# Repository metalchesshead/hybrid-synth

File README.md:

Analog/Digital Hybrid Synthesizer

How to use:
1. Draw wave envelope
2. Upload to board

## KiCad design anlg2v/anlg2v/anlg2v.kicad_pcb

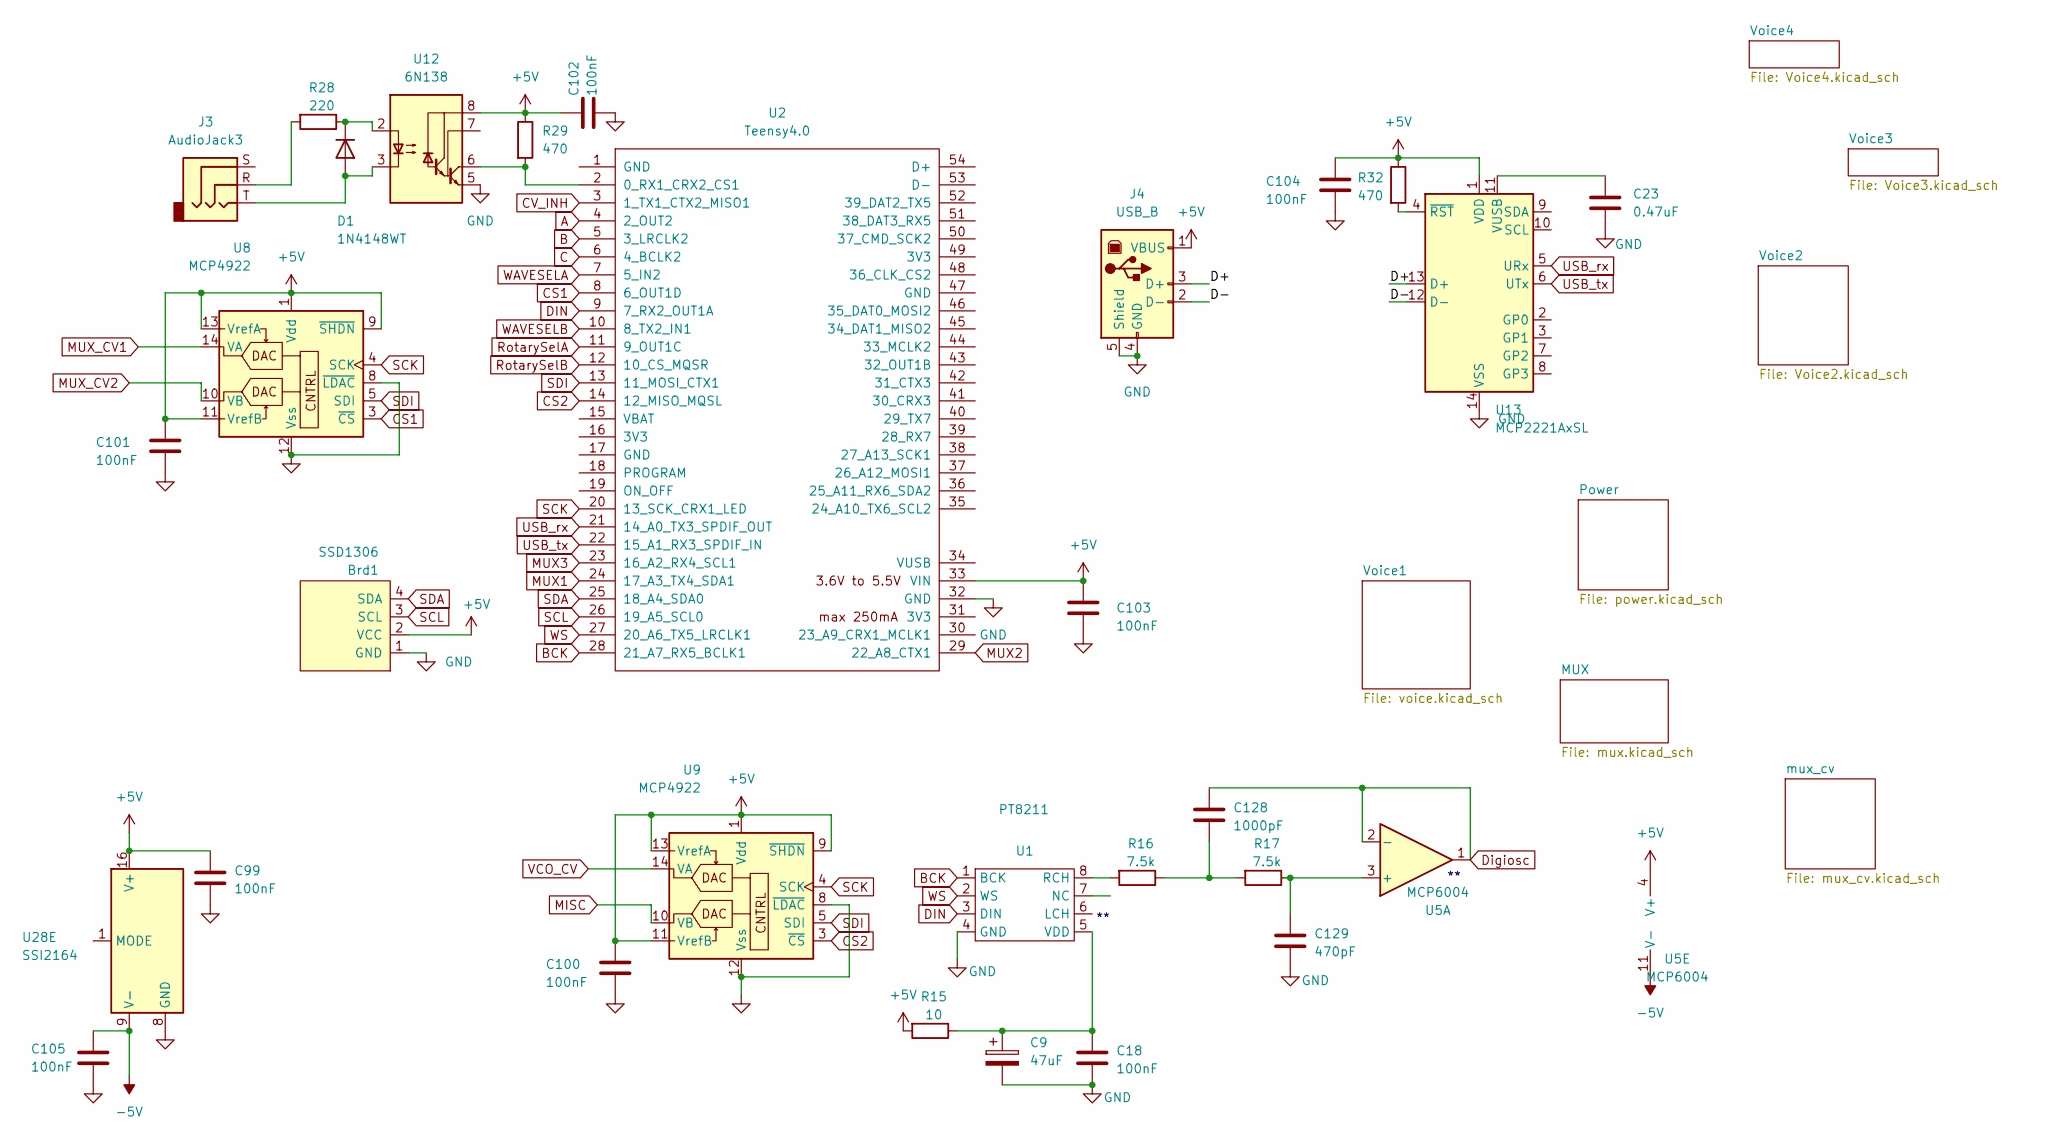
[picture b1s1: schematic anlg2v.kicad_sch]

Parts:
Brd1: SSD1306; 128x64OLED
C9: 47uF; CP_Radial_D10.0mm_P5.00mm
C18, C99, C100, C101, C102, C103, C104, C105: 100nF; C_0402_1005Metric_Pad0.74x0.62mm_HandSolder
C23: 0.47uF; C_0402_1005Metric_Pad0.74x0.62mm_HandSolder
C128: 1000pF; C_0402_1005Metric_Pad0.74x0.62mm_HandSolder
C129: 470pF; C_0402_1005Metric_Pad0.74x0.62mm_HandSolder
D1: 1N4148WT; D_SOD-523
J3: AudioJack3; PJ-307
J4: USB_B; USB_B_Lumberg_2411_02_Horizontal
R15: 10; R_0402_1005Metric
R16, R17: 7.5k; R_0402_1005Metric
R28: 220; R_0402_1005Metric
R29, R32: 470; R_0402_1005Metric
U1: PT8211; SOP-8_3.76x4.96mm_P1.27mm
U2: Teensy4.0; Teensy40
U5: MCP6004; SOIC-14_3.9x8.7mm_P1.27mm
U8, U9: MCP4922; SOIC-14_3.9x8.7mm_P1.27mm
U12: 6N138; DIP-8_W7.62mm_Socket
U13: MCP2221AxSL; SOIC-14_3.9x8.7mm_P1.27mm
U28: SSI2164; SOP-16_3.9x9.9mm_P1.27mm

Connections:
+5V: Brd1.2 (VCC), C99.1, C100.1, C101.1, C102.1, C103.1, C104.1, J4.1 (VBUS), R15.2, R29.1, R32.1, U2.33 (VIN), U5.4 (V+), U8.1 (Vdd), U8.9 (~SHDN), U8.11 (VrefB), U8.13 (VrefA), U9.1 (Vdd), U9.9 (~SHDN), U9.11 (VrefB), U9.13 (VrefA), U12.8 (VCC), U13.1 (VDD), U28.16 (V+); also elsewhere on the board
-5V: C105.1, U5.11 (V-), U28.9 (V-); also elsewhere on the board
/D+: J4.3 (D+), U13.13 (D+)
/D-: J4.2 (D-), U13.12 (D-)
A: U2.4 (2_OUT2); also elsewhere on the board
B: U2.5 (3_LRCLK2); also elsewhere on the board
BCK: U1.1 (BCK), U2.28 (21_A7_RX5_BCLK1)
C: U2.6 (4_BCLK2); also elsewhere on the board
CS1: U2.8 (6_OUT1D), U8.3 (~CS)
CS2: U2.14 (12_MISO_MQSL), U9.3 (~CS)
CV_INH: U2.3 (1_TX1_CTX2_MISO1); also elsewhere on the board
DIN: U1.3 (DIN), U2.9 (7_RX2_OUT1A)
GND: Brd1.1 (GND), C9.2, C18.2, C23.2, C99.2, C100.2, C101.2, C102.2, C103.2, C104.2, C105.2, C129.2, J4.4 (GND), J4.5 (Shield), U1.4 (GND), U1.6 (LCH), U2.32 (GND), U8.8 (~LDAC), U8.12 (Vss), U9.8 (~LDAC), U9.12 (Vss), U12.5 (GND), U13.14 (VSS), U28.8 (GND); also elsewhere on the board
MISC: U9.10 (VB)
MUX1: U2.24 (17_A3_TX4_SDA1); also elsewhere on the board
MUX2: U2.29 (22_A8_CTX1); also elsewhere on the board
MUX3: U2.23 (16_A2_RX4_SCL1); also elsewhere on the board
MUX_CV1: U8.14 (VA); also elsewhere on the board
MUX_CV2: U8.10 (VB); also elsewhere on the board
unnamed 22: C128.2, R16.1, R17.2; also elsewhere on the board
unnamed: D1.2 (A), J3.T, U12.3 (C2)
unnamed: D1.1 (K), R28.1, U12.2 (C1)
unnamed: J3.R, R28.2
unnamed: R16.2, U1.8 (RCH)
unnamed: C9.1, C18.1, R15.1, U1.5 (VDD)
unnamed: R29.2, U2.2 (0_RX1_CRX2_CS1), U12.6 (VO2)
unnamed: C23.1, U13.11 (VUSB)
unnamed: R32.2, U13.4 (~RST)
RotarySelA: U2.11 (9_OUT1C); also elsewhere on the board
RotarySelB: U2.12 (10_CS_MQSR); also elsewhere on the board
SCK: U2.20 (13_SCK_CRX1_LED), U8.4 (SCK), U9.4 (SCK)
SCL: Brd1.3 (SCL), U2.26 (19_A5_SCL0)
SDA: Brd1.4 (SDA), U2.25 (18_A4_SDA0)
SDI: U2.13 (11_MOSI_CTX1), U8.5 (SDI), U9.5 (SDI)
USB_rx: U2.21 (14_A0_TX3_SPDIF_OUT), U13.5 (URx)
USB_tx: U2.22 (15_A1_RX3_SPDIF_IN), U13.6 (UTx)
VCO_CV: U9.14 (VA); also elsewhere on the board
WAVESELA: U2.7 (5_IN2); also elsewhere on the board
WAVESELB: U2.10 (8_TX2_IN1); also elsewhere on the board
WS: U1.2 (WS), U2.27 (20_A6_TX5_LRCLK1)

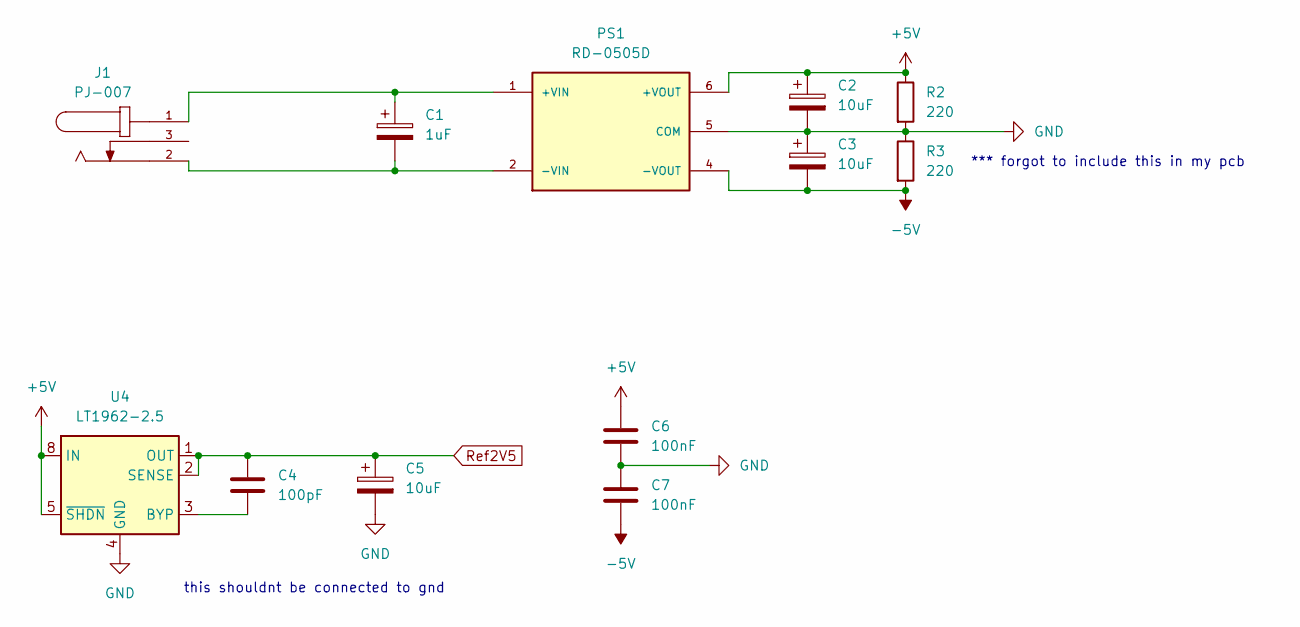
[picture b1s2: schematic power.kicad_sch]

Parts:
C1: 1uF; CP_Radial_D10.0mm_P5.00mm
C2, C3, C5: 10uF; CP_Radial_D10.0mm_P5.00mm
C4: 100pF; C_0402_1005Metric_Pad0.74x0.62mm_HandSolder
C6, C7: 100nF; C_0402_1005Metric_Pad0.74x0.62mm_HandSolder
J1: PJ-007; SAMESKY_PJ-007; PARTREV 1.07
PS1: RD-0505D; CONV_RD-0505D; PARTREV 1
R2, R3: 220; R_0402_1005Metric
U4: LT1962-2.5; MSOP-8_3x3mm_P0.65mm

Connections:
+5V: C2.1, C6.1, PS1.6 (+VOUT), R2.1, U4.5 (~SHDN), U4.8 (IN); also elsewhere on the board
-5V: C3.2, C7.2, PS1.4 (-VOUT), R3.2; also elsewhere on the board
GND: C2.2, C3.1, C5.2, C6.2, C7.1, PS1.5 (COM), R2.2, R3.1, U4.4 (GND); also elsewhere on the board
unnamed: C1.1, J1.1, PS1.1 (+VIN)
unnamed: C1.2, J1.2, PS1.2 (-VIN)
unnamed: C4.2, U4.3 (BYP)
Ref2V5: C4.1, C5.1, U4.1 (OUT), U4.2 (SENSE); also elsewhere on the board

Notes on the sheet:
this shouldnt be connected to gnd
*** forgot to include this in my pcb

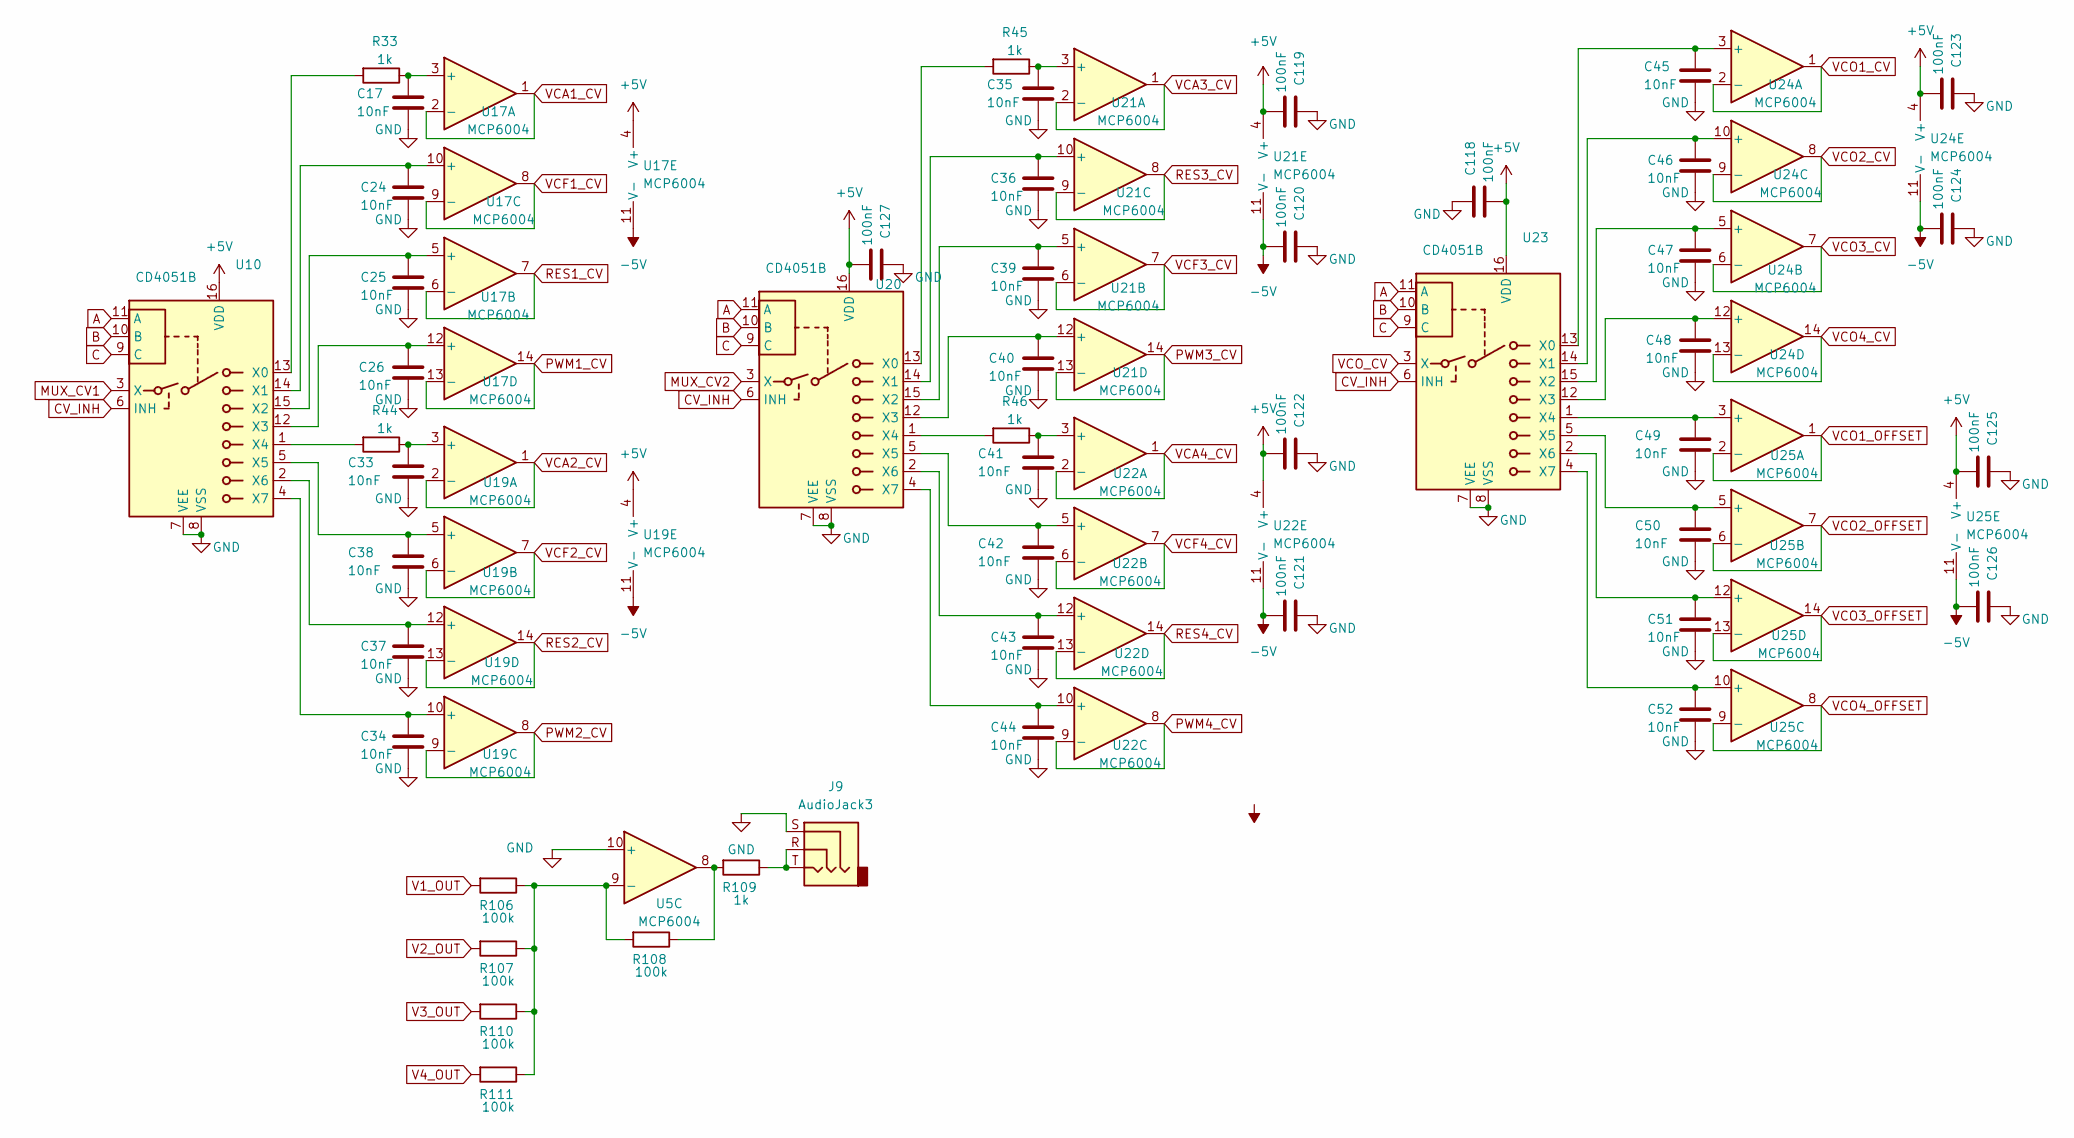
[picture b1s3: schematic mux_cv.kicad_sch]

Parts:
C17, C24, C25, C26, C33, C34, C35, C36, C37, C38, C39, C40, C41, C42, C43, C44, C45, C46, C47, C48, C49, C50, C51, C52: 10nF; C_0402_1005Metric_Pad0.74x0.62mm_HandSolder
C118, C119, C120, C121, C122, C123, C124, C125, C126, C127: 100nF; C_0402_1005Metric_Pad0.74x0.62mm_HandSolder
J9: AudioJack3; PJ-307
R33, R44, R45, R46, R109: 1k; R_0402_1005Metric
R106, R107, R108, R110, R111: 100k; R_0402_1005Metric
U5, U17, U19, U21, U22, U24, U25: MCP6004; SOIC-14_3.9x8.7mm_P1.27mm
U10, U20, U23: CD4051B; SOIC-16_3.9x9.9mm_P1.27mm

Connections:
+5V: C118.2, C119.2, C122.2, C123.2, C125.2, C127.2, U10.16 (VDD), U17.4 (V+), U19.4 (V+), U20.16 (VDD), U21.4 (V+), U22.4 (V+), U23.16 (VDD), U24.4 (V+), U25.4 (V+); also elsewhere on the board
-5V: C120.2, C121.2, C124.2, C126.2, U17.11 (V-), U19.11 (V-), U21.11 (V-), U22.11 (V-), U24.11 (V-), U25.11 (V-); also elsewhere on the board
A: U10.11 (A), U20.11 (A), U23.11 (A); also elsewhere on the board
B: U10.10 (B), U20.10 (B), U23.10 (B); also elsewhere on the board
C: U10.9 (C), U20.9 (C), U23.9 (C); also elsewhere on the board
CV_INH: U10.6 (INH), U20.6 (INH), U23.6 (INH); also elsewhere on the board
GND: C17.2, C24.2, C25.2, C26.2, C33.2, C34.2, C35.2, C36.2, C37.2, C38.2, C39.2, C40.2, C41.2, C42.2, C43.2, C44.2, C45.2, C46.2, C47.2, C48.2, C49.2, C50.2, C51.2, C52.2, C118.1, C119.1, C120.1, C121.1, C122.1, C123.1, C124.1, C125.1, C126.1, C127.1, J9.S, U5.10 (+), U10.7 (VEE), U10.8 (VSS), U20.7 (VEE), U20.8 (VSS), U23.7 (VEE), U23.8 (VSS); also elsewhere on the board
MUX_CV1: U10.3 (X); also elsewhere on the board
MUX_CV2: U20.3 (X); also elsewhere on the board
unnamed: J9.R, J9.T, R109.1
unnamed: R108.1, R109.2, U5.8
unnamed: R106.1, R107.1, R108.2, R110.1, R111.1, U5.9 (-)
unnamed: R33.2, U10.13 (X0)
unnamed: C24.1, U10.14 (X1), U17.10 (+)
unnamed: C25.1, U10.15 (X2), U17.5 (+)
unnamed: C26.1, U10.12 (X3), U17.12 (+)
unnamed: R44.2, U10.1 (X4)
unnamed: C38.1, U10.5 (X5), U19.5 (+)
unnamed: C37.1, U10.2 (X6), U19.12 (+)
unnamed: C34.1, U10.4 (X7), U19.10 (+)
unnamed: C17.1, R33.1, U17.3 (+)
unnamed: C33.1, R44.1, U19.3 (+)
unnamed: R45.2, U20.13 (X0)
unnamed: C36.1, U20.14 (X1), U21.10 (+)
unnamed: C39.1, U20.15 (X2), U21.5 (+)
unnamed: C40.1, U20.12 (X3), U21.12 (+)
unnamed: R46.2, U20.1 (X4)
unnamed: C42.1, U20.5 (X5), U22.5 (+)
unnamed: C43.1, U20.2 (X6), U22.12 (+)
unnamed: C44.1, U20.4 (X7), U22.10 (+)
unnamed: C35.1, R45.1, U21.3 (+)
unnamed: C41.1, R46.1, U22.3 (+)
unnamed: C45.1, U23.13 (X0), U24.3 (+)
unnamed: C46.1, U23.14 (X1), U24.10 (+)
unnamed: C47.1, U23.15 (X2), U24.5 (+)
unnamed: C48.1, U23.12 (X3), U24.12 (+)
unnamed: C49.1, U23.1 (X4), U25.3 (+)
unnamed: C50.1, U23.5 (X5), U25.5 (+)
unnamed: C51.1, U23.2 (X6), U25.12 (+)
unnamed: C52.1, U23.4 (X7), U25.10 (+)
PWM1_CV: U17.13 (-), U17.14; also elsewhere on the board
PWM2_CV: U19.8, U19.9 (-); also elsewhere on the board
PWM3_CV: U21.13 (-), U21.14; also elsewhere on the board
PWM4_CV: U22.8, U22.9 (-); also elsewhere on the board
RES1_CV: U17.6 (-), U17.7; also elsewhere on the board
RES2_CV: U19.13 (-), U19.14; also elsewhere on the board
RES3_CV: U21.8, U21.9 (-); also elsewhere on the board
RES4_CV: U22.13 (-), U22.14; also elsewhere on the board
V1_OUT: R106.2; also elsewhere on the board
V2_OUT: R107.2; also elsewhere on the board
V3_OUT: R110.2; also elsewhere on the board
V4_OUT: R111.2; also elsewhere on the board
VCA1_CV: U17.1, U17.2 (-); also elsewhere on the board
VCA2_CV: U19.1, U19.2 (-); also elsewhere on the board
VCA3_CV: U21.1, U21.2 (-); also elsewhere on the board
VCA4_CV: U22.1, U22.2 (-); also elsewhere on the board
VCF1_CV: U17.8, U17.9 (-); also elsewhere on the board
VCF2_CV: U19.6 (-), U19.7; also elsewhere on the board
VCF3_CV: U21.6 (-), U21.7; also elsewhere on the board
VCF4_CV: U22.6 (-), U22.7; also elsewhere on the board
VCO1_CV: U24.1, U24.2 (-); also elsewhere on the board
VCO1_OFFSET: U25.1, U25.2 (-); also elsewhere on the board
VCO2_CV: U24.8, U24.9 (-); also elsewhere on the board
VCO2_OFFSET: U25.6 (-), U25.7; also elsewhere on the board
VCO3_CV: U24.6 (-), U24.7; also elsewhere on the board
VCO3_OFFSET: U25.13 (-), U25.14; also elsewhere on the board
VCO4_CV: U24.13 (-), U24.14; also elsewhere on the board
VCO4_OFFSET: U25.8, U25.9 (-); also elsewhere on the board
VCO_CV: U23.3 (X); also elsewhere on the board

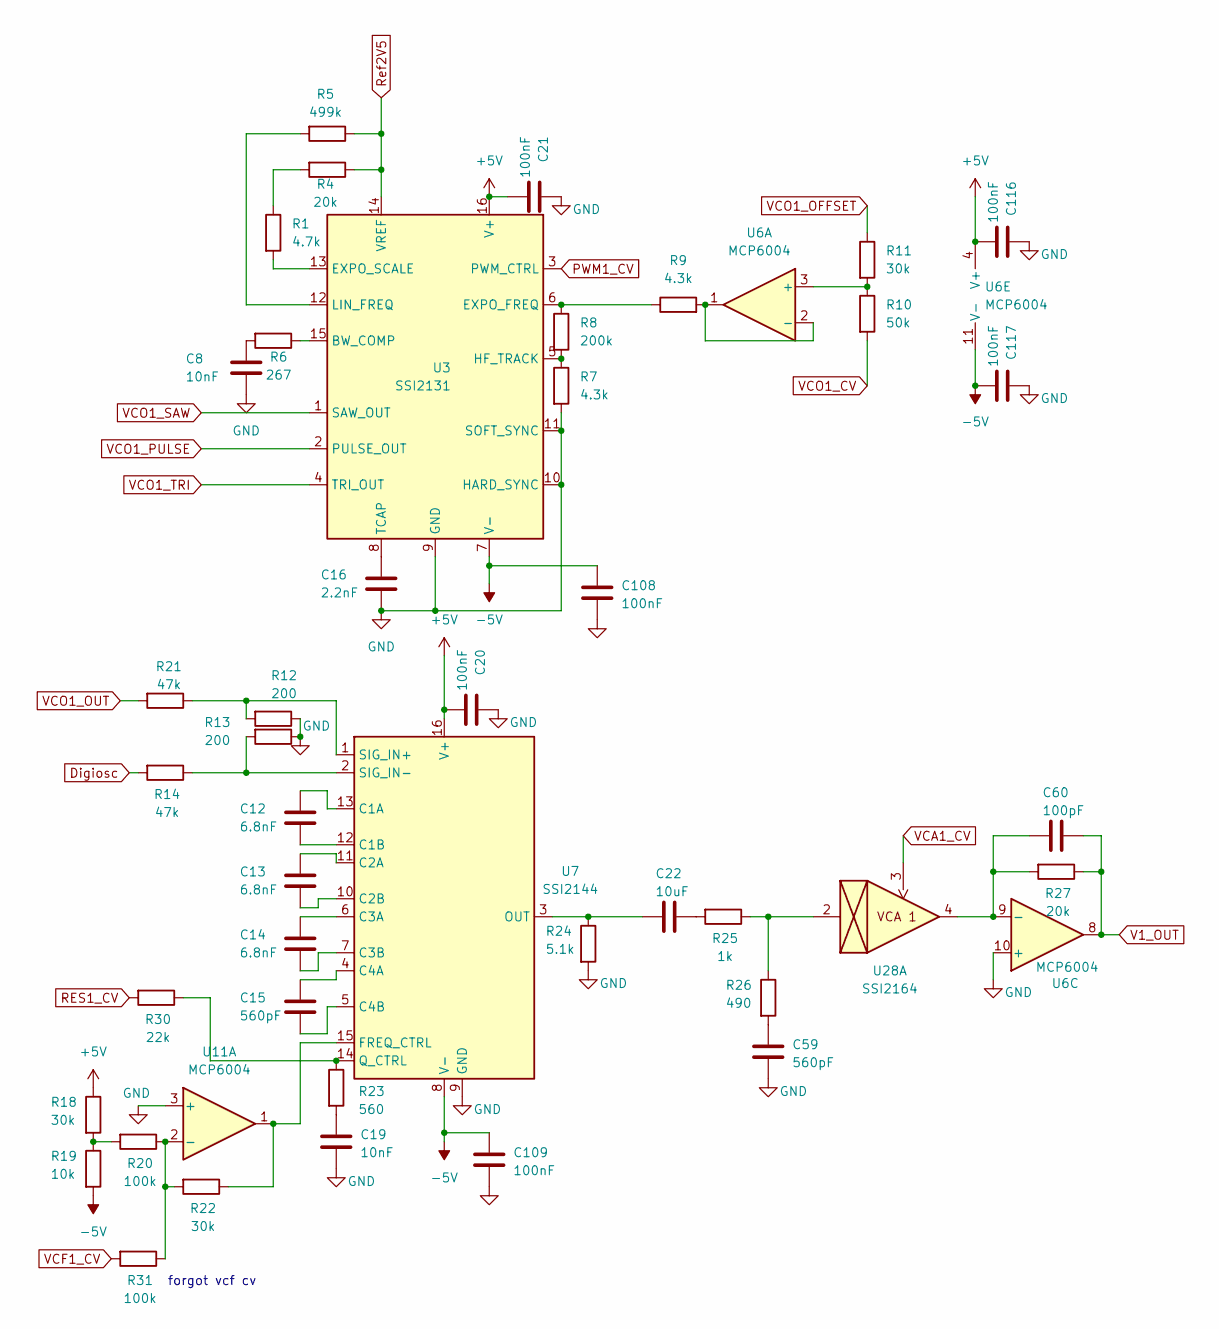
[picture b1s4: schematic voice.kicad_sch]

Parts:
C8, C19: 10nF; C_0402_1005Metric_Pad0.74x0.62mm_HandSolder
C12, C13, C14: 6.8nF; C_0402_1005Metric_Pad0.74x0.62mm_HandSolder
C15, C59: 560pF; C_0402_1005Metric_Pad0.74x0.62mm_HandSolder
C16: 2.2nF; C_0402_1005Metric_Pad0.74x0.62mm_HandSolder
C20, C21, C108, C109, C116, C117: 100nF; C_0402_1005Metric_Pad0.74x0.62mm_HandSolder
C22: 10uF; C_0402_1005Metric_Pad0.74x0.62mm_HandSolder
C60: 100pF; C_0402_1005Metric_Pad0.74x0.62mm_HandSolder
R1: 4.7k; R_0402_1005Metric
R4, R27: 20k; R_0402_1005Metric
R5: 499k; R_0402_1005Metric
R6: 267; R_0402_1005Metric
R7, R9: 4.3k; R_0402_1005Metric
R8: 200k; R_0402_1005Metric
R10: 50k; R_0402_1005Metric
R11, R18, R22: 30k; R_0402_1005Metric
R12, R13: 200; R_0402_1005Metric
R14, R21: 47k; R_0402_1005Metric
R19: 10k; R_0402_1005Metric
R20, R31: 100k; R_0402_1005Metric
R23: 560; R_0402_1005Metric
R24: 5.1k; R_0402_1005Metric
R25: 1k; R_0402_1005Metric
R26: 490; R_0402_1005Metric
R30: 22k; R_0402_1005Metric
U3: SSI2131; STC_SOP-16_3.9x9.9mm_P1.27mm
U6, U11: MCP6004; SOIC-14_3.9x8.7mm_P1.27mm
U7: SSI2144; SSOP-16_3.9x4.9mm_P0.635mm
U28: SSI2164; STC_SOP-16_3.9x9.9mm_P1.27mm

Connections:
+5V: C20.2, C21.2, C116.2, R18.1, U3.16 (V+), U6.4 (V+), U7.16 (V+); also elsewhere on the board
-5V: C108.1, C109.1, C117.2, R19.2, U3.7 (V-), U6.11 (V-), U7.8 (V-); also elsewhere on the board
GND: C8.2, C16.2, C19.2, C20.1, C21.1, C59.2, C108.2, C109.2, C116.1, C117.1, R7.2, R12.1, R13.1, R24.2, U3.9 (GND), U3.10 (HARD_SYNC), U3.11 (SOFT_SYNC), U6.10 (+), U7.9 (GND), U11.3 (+); also elsewhere on the board
unnamed: C8.1, R6.2
unnamed: C19.1, R23.2
unnamed: C22.2, R25.2
unnamed: C59.1, R26.2
unnamed: R1.1, R4.2
unnamed: R18.2, R19.1, R20.2
unnamed: R25.1, R26.1, U28.2
unnamed: R6.1, U3.15 (BW_COMP)
unnamed: R8.1, R9.1, U3.6 (EXPO_FREQ)
unnamed: R1.2, U3.13 (EXPO_SCALE)
unnamed: R7.1, R8.2, U3.5 (HF_TRACK)
unnamed: R5.2, U3.12 (LIN_FREQ)
unnamed: C16.1, U3.8 (TCAP)
unnamed: R10.1, R11.2, U6.3 (+)
unnamed: R9.2, U6.1, U6.2 (-)
unnamed: C60.1, R27.2, U6.9 (-), U28.4
unnamed: C12.1, U7.13 (C1A)
unnamed: C12.2, U7.12 (C1B)
unnamed: C13.1, U7.11 (C2A)
unnamed: C13.2, U7.10 (C2B)
unnamed: C14.1, U7.6 (C3A)
unnamed: C14.2, U7.7 (C3B)
unnamed: C15.1, U7.4 (C4A)
unnamed: C15.2, U7.5 (C4B)
unnamed: R22.1, U7.15 (FREQ_CTRL), U11.1
unnamed: C22.1, R24.1, U7.3 (OUT)
unnamed: R23.1, R30.1, U7.14 (Q_CTRL)
unnamed: R12.2, R21.1, U7.1 (SIG_IN+)
unnamed: R13.2, R14.1, U7.2 (SIG_IN-)
unnamed: R20.1, R22.2, R31.1, U11.2 (-)
PWM1_CV: U3.3 (PWM_CTRL); also elsewhere on the board
RES1_CV: R30.2; also elsewhere on the board
Ref2V5: R4.1, R5.1, U3.14 (VREF); also elsewhere on the board
V1_OUT: C60.2, R27.1, U6.8; also elsewhere on the board
VCA1_CV: U28.3; also elsewhere on the board
VCF1_CV: R31.2; also elsewhere on the board
VCO1_CV: R10.2; also elsewhere on the board
VCO1_OFFSET: R11.1; also elsewhere on the board
VCO1_OUT: R21.2; also elsewhere on the board
VCO1_PULSE: U3.2 (PULSE_OUT); also elsewhere on the board
VCO1_SAW: U3.1 (SAW_OUT); also elsewhere on the board
VCO1_TRI: U3.4 (TRI_OUT); also elsewhere on the board

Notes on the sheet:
forgot vcf cv

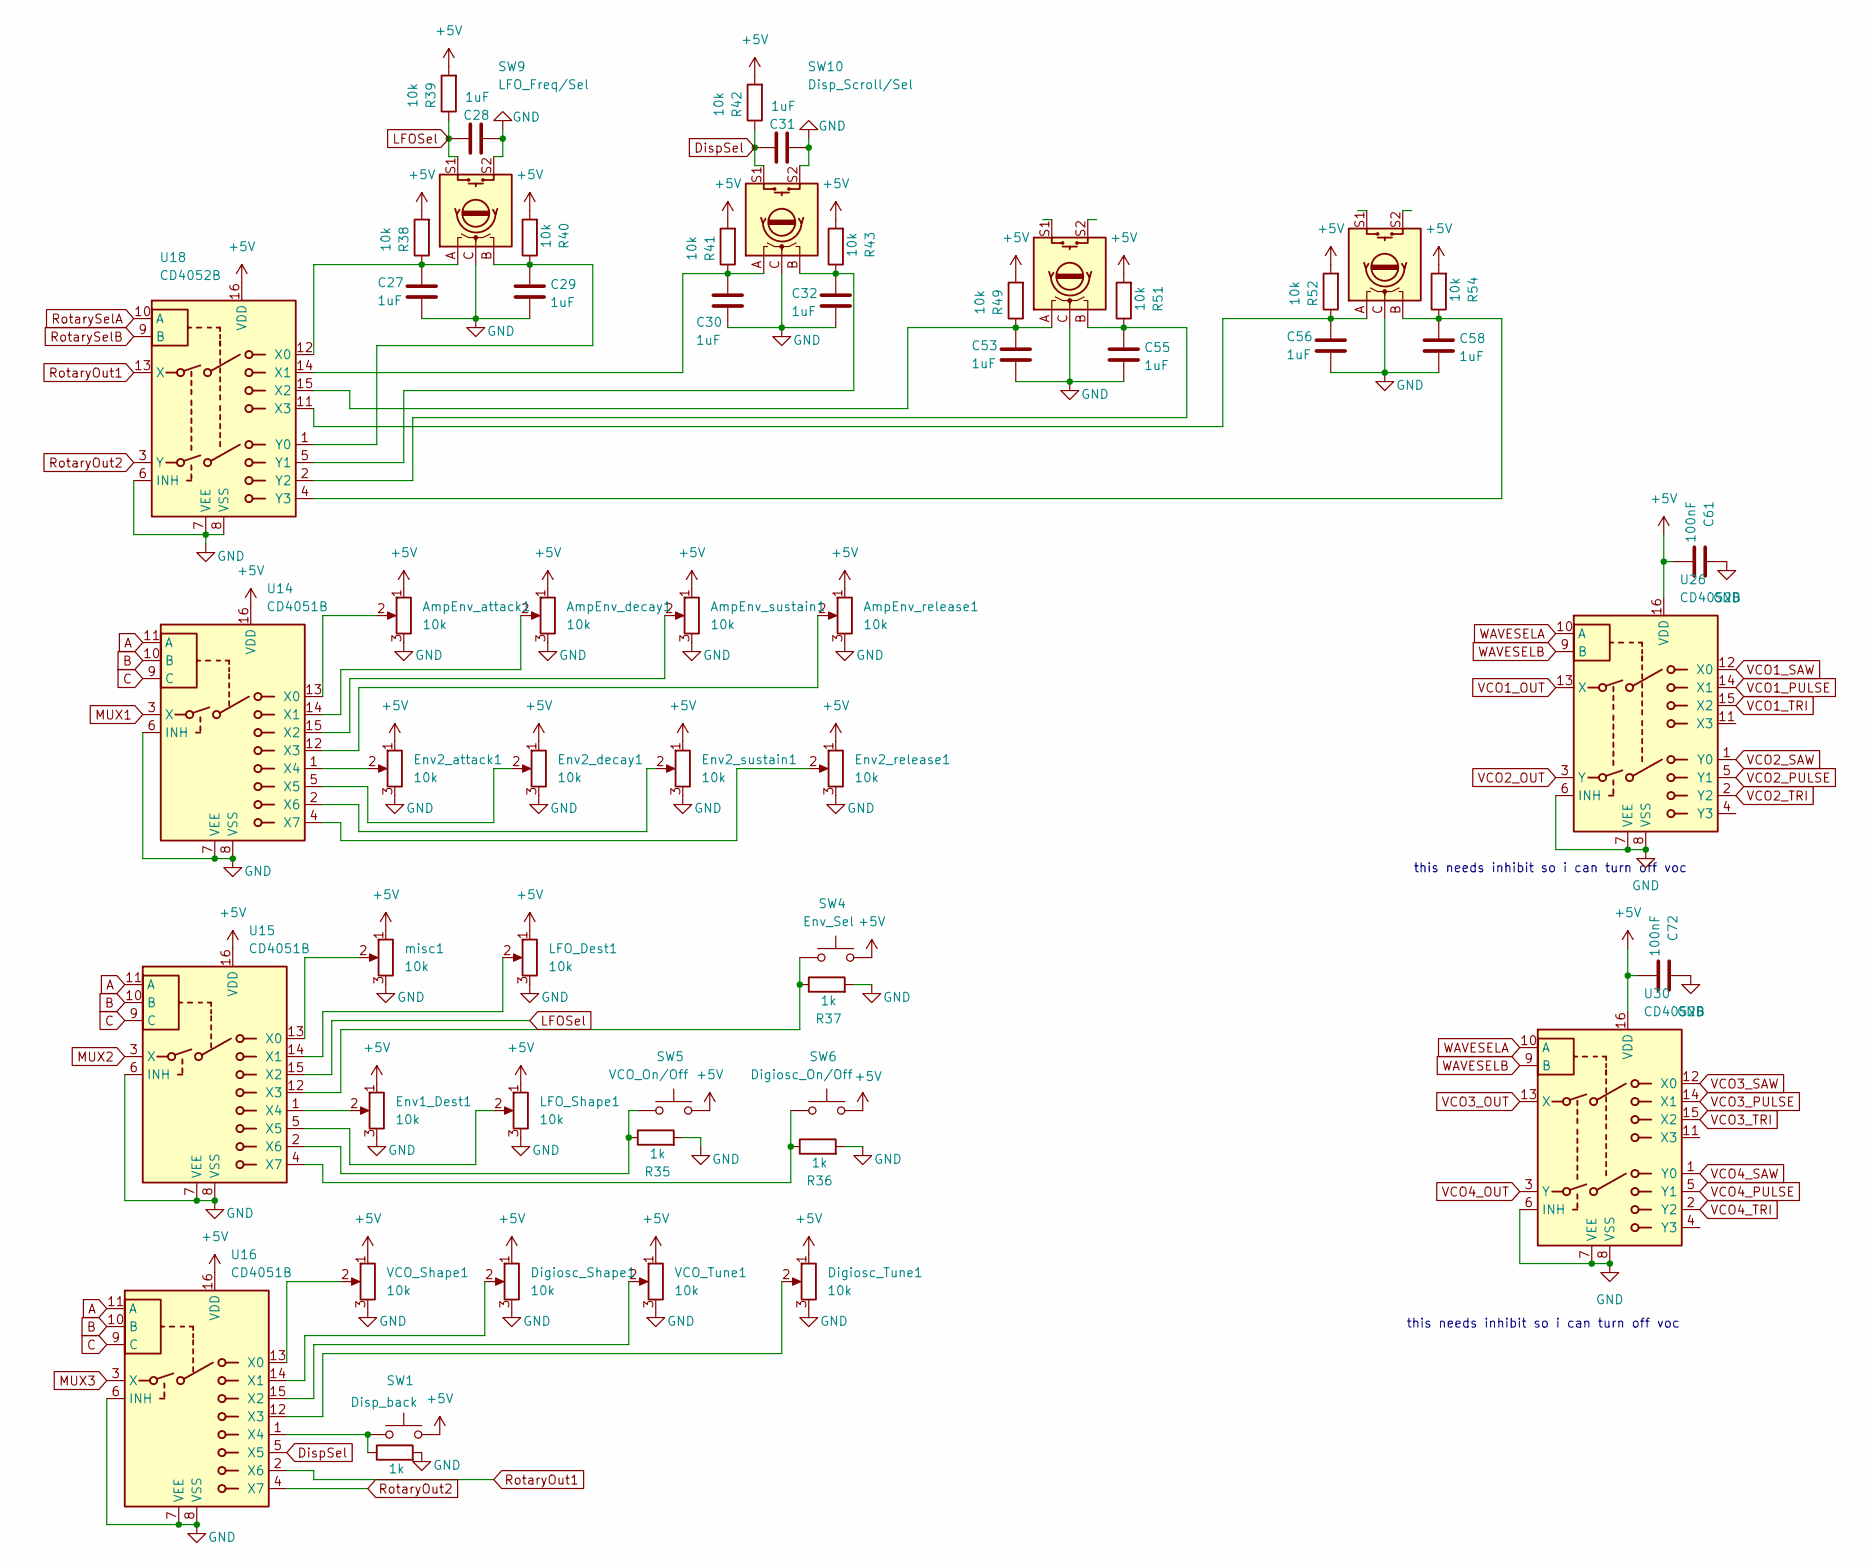
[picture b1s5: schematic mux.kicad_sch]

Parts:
AmpEnv_attack1: 10k; Potentiometer_Bourns_PTA3043_Single_Slide
AmpEnv_decay1: 10k; Potentiometer_Bourns_PTA3043_Single_Slide
AmpEnv_release1: 10k; Potentiometer_Bourns_PTA3043_Single_Slide
AmpEnv_sustain1: 10k; Potentiometer_Bourns_PTA3043_Single_Slide
C27, C28, C29, C30, C31, C32, C53, C55, C56, C58: 1uF; C_0402_1005Metric_Pad0.74x0.62mm_HandSolder
C61, C72: 100nF; C_0402_1005Metric_Pad0.74x0.62mm_HandSolder
Digiosc_Shape1: 10k; Potentiometer_Bourns_PTV09A-1_Single_Vertical
Digiosc_Tune1: 10k; Potentiometer_Bourns_PTV09A-1_Single_Vertical
Env1_Dest1: 10k; Potentiometer_Bourns_PTV09A-1_Single_Vertical
Env2_attack1, Env2_decay1, Env2_release1, Env2_sustain1: 10k; Potentiometer_Bourns_PTA3043_Single_Slide
LFO_Dest1: 10k; Potentiometer_Bourns_PTV09A-1_Single_Vertical
LFO_Shape1: 10k; Potentiometer_Bourns_PTV09A-1_Single_Vertical
R34, R35, R36, R37: 1k; R_0402_1005Metric
R38, R39, R40, R41, R42, R43, R49, R51, R52, R54: 10k; R_0402_1005Metric
SW1: Disp_back; SW_TH_Tactile_Omron_B3F-102x
SW4: Env_Sel; SW_TH_Tactile_Omron_B3F-102x
SW5: VCO_On/Off; SW_TH_Tactile_Omron_B3F-102x
SW6: Digiosc_On/Off; SW_TH_Tactile_Omron_B3F-102x
SW9: LFO_Freq/Sel; RotaryEncoder_Bourns_Vertical_PEC12R-3x17F-Sxxxx
SW10: Disp_Scroll/Sel; RotaryEncoder_Bourns_Vertical_PEC12R-3x17F-Sxxxx
SW11: Misc1; RotaryEncoder_Bourns_Vertical_PEC12R-3x17F-Sxxxx
SW12: Misc2; RotaryEncoder_Bourns_Vertical_PEC12R-3x17F-Sxxxx
U14, U15, U16: CD4051B; SOIC-16_3.9x9.9mm_P1.27mm
U18, U26, U30: CD4052B; SOIC-16_3.9x9.9mm_P1.27mm
VCO_Shape1: 10k; Potentiometer_Bourns_PTV09A-1_Single_Vertical
VCO_Tune1: 10k; Potentiometer_Bourns_PTV09A-1_Single_Vertical
misc1: 10k; Potentiometer_Bourns_PTV09A-1_Single_Vertical

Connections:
+5V: AmpEnv_attack1.1, AmpEnv_decay1.1, AmpEnv_release1.1, AmpEnv_sustain1.1, C61.2, C72.2, Digiosc_Shape1.1, Digiosc_Tune1.1, Env1_Dest1.1, Env2_attack1.1, Env2_decay1.1, Env2_release1.1, Env2_sustain1.1, LFO_Dest1.1, LFO_Shape1.1, R38.2, R39.2, R40.2, R41.2, R42.2, R43.2, R49.2, R51.2, R52.2, R54.2, SW1.2, SW4.2, SW5.2, SW6.2, U14.16 (VDD), U15.16 (VDD), U16.16 (VDD), U18.16 (VDD), U26.16 (VDD), U30.16 (VDD), VCO_Shape1.1, VCO_Tune1.1, misc1.1; also elsewhere on the board
A: U14.11 (A), U15.11 (A), U16.11 (A); also elsewhere on the board
B: U14.10 (B), U15.10 (B), U16.10 (B); also elsewhere on the board
C: U14.9 (C), U15.9 (C), U16.9 (C); also elsewhere on the board
DispSel: C31.2, R42.1, SW10.S1, U16.5 (X5)
GND: AmpEnv_attack1.3, AmpEnv_decay1.3, AmpEnv_release1.3, AmpEnv_sustain1.3, C27.2, C28.1, C29.2, C30.2, C31.1, C32.2, C53.2, C55.2, C56.2, C58.2, C61.1, C72.1, Digiosc_Shape1.3, Digiosc_Tune1.3, Env1_Dest1.3, Env2_attack1.3, Env2_decay1.3, Env2_release1.3, Env2_sustain1.3, LFO_Dest1.3, LFO_Shape1.3, R34.2, R35.2, R36.2, R37.2, SW9.C, SW9.S2, SW10.C, SW10.S2, SW11.C, SW12.C, U14.6 (INH), U14.7 (VEE), U14.8 (VSS), U15.6 (INH), U15.7 (VEE), U15.8 (VSS), U16.6 (INH), U16.7 (VEE), U16.8 (VSS), U18.6 (INH), U18.7 (VEE), U18.8 (VSS), U26.6 (INH), U26.7 (VEE), U26.8 (VSS), U30.6 (INH), U30.7 (VEE), U30.8 (VSS), VCO_Shape1.3, VCO_Tune1.3, misc1.3; also elsewhere on the board
LFOSel: C28.2, R39.1, SW9.S1, U15.15 (X2)
MUX1: U14.3 (X); also elsewhere on the board
MUX2: U15.3 (X); also elsewhere on the board
MUX3: U16.3 (X); also elsewhere on the board
unnamed: AmpEnv_attack1.2, U14.13 (X0)
unnamed: AmpEnv_decay1.2, U14.14 (X1)
unnamed: AmpEnv_sustain1.2, U14.15 (X2)
unnamed: AmpEnv_release1.2, U14.12 (X3)
unnamed: Env2_attack1.2, U14.1 (X4)
unnamed: Env2_decay1.2, U14.5 (X5)
unnamed: Env2_sustain1.2, U14.2 (X6)
unnamed: Env2_release1.2, U14.4 (X7)
unnamed: U15.13 (X0), misc1.2
unnamed: LFO_Dest1.2, U15.14 (X1)
unnamed: R37.1, SW4.1, U15.12 (X3)
unnamed: Env1_Dest1.2, U15.1 (X4)
unnamed: LFO_Shape1.2, U15.5 (X5)
unnamed: R35.1, SW5.1, U15.2 (X6)
unnamed: R36.1, SW6.1, U15.4 (X7)
unnamed: U16.13 (X0), VCO_Shape1.2
unnamed: Digiosc_Shape1.2, U16.14 (X1)
unnamed: U16.15 (X2), VCO_Tune1.2
unnamed: Digiosc_Tune1.2, U16.12 (X3)
unnamed: R34.1, SW1.1, U16.1 (X4)
unnamed: C27.1, R38.1, SW9.A, U18.12 (X0)
unnamed: C30.1, R41.1, SW10.A, U18.14 (X1)
unnamed: C53.1, R49.1, SW11.A, U18.15 (X2)
unnamed: C56.1, R52.1, SW12.A, U18.11 (X3)
unnamed: C29.1, R40.1, SW9.B, U18.1 (Y0)
unnamed: C32.1, R43.1, SW10.B, U18.5 (Y1)
unnamed: C55.1, R51.1, SW11.B, U18.2 (Y2)
unnamed: C58.1, R54.1, SW12.B, U18.4 (Y3)
RotaryOut1: U16.2 (X6), U18.13 (X)
RotaryOut2: U16.4 (X7), U18.3 (Y)
RotarySelA: U18.10 (A); also elsewhere on the board
RotarySelB: U18.9 (B); also elsewhere on the board
VCO1_OUT: U26.13 (X); also elsewhere on the board
VCO1_PULSE: U26.14 (X1); also elsewhere on the board
VCO1_SAW: U26.12 (X0); also elsewhere on the board
VCO1_TRI: U26.15 (X2); also elsewhere on the board
VCO2_OUT: U26.3 (Y); also elsewhere on the board
VCO2_PULSE: U26.5 (Y1); also elsewhere on the board
VCO2_SAW: U26.1 (Y0); also elsewhere on the board
VCO2_TRI: U26.2 (Y2); also elsewhere on the board
VCO3_OUT: U30.13 (X); also elsewhere on the board
VCO3_PULSE: U30.14 (X1); also elsewhere on the board
VCO3_SAW: U30.12 (X0); also elsewhere on the board
VCO3_TRI: U30.15 (X2); also elsewhere on the board
VCO4_OUT: U30.3 (Y); also elsewhere on the board
VCO4_PULSE: U30.5 (Y1); also elsewhere on the board
VCO4_SAW: U30.1 (Y0); also elsewhere on the board
VCO4_TRI: U30.2 (Y2); also elsewhere on the board
WAVESELA: U26.10 (A), U30.10 (A); also elsewhere on the board
WAVESELB: U26.9 (B), U30.9 (B); also elsewhere on the board

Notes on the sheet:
this needs inhibit so i can turn off voc
